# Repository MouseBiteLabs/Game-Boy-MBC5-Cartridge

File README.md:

# Game Boy MBC5 Cartridge

This is my design of a flashable MBC5-based cartridge for the Game Boy. The MBC5 mapper greatly augments the memory access of the Game Boy for larger games. Most of the games that came out in the last years of the Game Boy and Game Boy Color used the MBC5 mapper.

This circuit board should cover most MBC5 games. The features are as follows:

- Able to make games up to 4 MB in size, that use up to 1 Mbit of RAM
- Compatibility with all four of the popular Game Boy battery management ICs - MM1026, MM1134, BA6129, and BA6735
- The option to add battery backup to the cartridge *without* the need of the original battery management ICs - perfect for MBC5 donors that didn't have batteries in them
- Fully compatible with the <a href="https://www.gbxcart.com/">GBxCart RW</a> so you can transfer games and save files to and from the board

All gerbers and source files can be found in this repo, as this project is fully open source. Technical documentation of the board can be found in the Technical folder.

## Important Things Before You Start

1) To use this board, you need to have an original Game Boy game that uses an MBC5 mapper chip. <a href="https://catskull.net/gb-rom-database/">You can find a list of games and their mappers here</a>. Use the search function. Please note the RAM is in bytes, not bits. Since SRAM in this repo is defined in bits, you need to convert by multiplying the number of bytes by 8.
2) You will need to remove the MBC5 from your donor cartridge for use on this board. This will require a hot air rework station or a hot plate. There's a list below of other parts you can re-use from the donor cartridge.
3) When soldering parts on, it's a good idea to put kapton tape or otherwise cover the bottom cartridge edge. You do not want to get solder on the cartridge contacts.
4) I am not responsible for any damage you do to your self or your property. Attempt this project at your own risk.
5) I do not guarantee design compatibility. You may encounter issues with certain games. There is also a chance I have made an error in the design or the BOM - if this is the case, I will do everything I can to address the problem as quickly as possible.
6) If you are using this board to make games other than for personal use, you must have permission from the originator to use and distribute any ROM images or other related material. You are responsible for making sure you adhere to any license requirements.

DO NOT use my circuit boards for profiting from stolen work - this especially includes homebrew content, ROM hacks, and using fan-made labels without permission from the originator. **Support original creators!**

## Board Characteristics and Order Information

The zipped folder contains all the gerber files for this board. The following options **must** be chosen when ordering boards for yourself.

- Thickness: 0.8mm
- Surface Finish: ENIG
- Gold Fingers: Yes, 30° chamfer

**I sell this blank circuit board on Etsy, so you don't have to buy a bunch of multiples if you don't want to.** (Click the banner!)

You can use the zipped folder at any board fabricator you like. You may also buy the board from PCBWay using this link (disclosure: I receive 10% of the sale value to go towards future PCB orders of my own):

<a href="https://oshpark.com/shared_projects/rcPGJGK0">The board is also listed on OSH Park as well.</a> **Be sure to get them in 0.8mm thickness if you order from here.**

## Required Equipment

The EEPROMs on the board needs to be programmed somehow. I recommend using the GBxCart, as mentioned. These boards are fully compatible with it, and it makes reflashing games extremely easy using <a href="https://github.com/lesserkuma/FlashGBX">lesserkuma's FlashGBX software</a>.

Alternatively, you can buy an EEPROM programmer with a TSOP adapter. The downside to this method is that you have to desolder the chip every time you want to program it. The <a href="https://flashcatusb.com/">FlashcatUSB</a> is one popular option in retro spaces.

## Battery Safety

When assembling a board, I recommend populating all the parts *except* the battery, and getting it to run initially without it. This is to make it easier to fix any solder connections that might need fixing, without having to worry about getting the battery hot. And if you need to rework anything near the battery after you've put it on the board, be safe and remove it before putting a hot soldering iron next to it.

And this should go without saying, but if you're assembling these boards with a hot plate or hot air, *do not* solder the battery on this way. You should use an iron, and keep heat off of the battery as much as possible. 

(Also check polarity!)

## Board Configurations

The board comes with three sets of jumper pads for solder bridges. SJ1 and SJ2 require you to solder bridge the middle pad either to the left or right pads. SJ3 is configured by either leaving the pads unsoldered or bridging them with solder. Here are the situations where you need to add solder bridges.

### SRAM Size Selection (SJ1 and SJ2, or SW1)

These jumpers are located underneath the MBC5 chip, and labeled "64K" and "256K/1M". Solder them to configure the amount of RAM your cart uses. You must configure these pads for every game you make, unless you do not need RAM. <a href="https://catskull.net/gb-rom-database/">You can find a list of games here with their respective RAM sizes.</a>

- If the game you're making uses 256 Kbit or 1 Mbit of RAM, then solder the middle pads of the two jumper sets to the right pads.
- If the game you're making uses 64 Kbit of RAM, then solder the middle pads of the two jumper sets to the left pads.
- SJ1 and SJ2 must be soldered in the same direction.
- The footprint of these selection pads should allow for a DPDT switch, part number CAS-220A1, to be placed on these pads instead of having to bridge the pads with solder.

Note that you can make games that only require 64 Kbit of RAM and still use a 256 Kbit or 1 Mbit SRAM chip. You still need to configure the jumpers to the 64Kb setting, though.

**I recommend using 64 Kbit or 256 Kbit RAM chips, unless you absolutely need 1 Mbit for the game you are making.**

### Using an MM1134 or BA6735 for U4 (SJ3)

Bridge the jumper SJ3 if you have either an MM1134 or BA6735 for U4, specifically. Any other battery management IC must leave SJ3 unsoldered.

## Test Points and Final Checkout

On the back of the board are five test points. Here's where they are connected:

- TP1: SRAM supply voltage
- TP2: Battery voltage (after R1)
- TP3: Battery voltage (positive terminal of battery)
- TP4: Ground
- TP5: VCC input voltage

After you assemble your game, you should measure the current out of the battery. But first, you should program it with the GBxCart, or if you programmed the EEPROM separately, put it into a Game Boy and cycle power once. Then, flip the PCB upside down on a non-conductive surface (not your leg), and set your multimeter in DC millivolts (or volts). Put the positive probe on TP3 and the negative probe on TP2. If you used a 10kΩ for R1, as indicated in the BOM, you should read a voltage in the single of millivolts. If you have something much higher, especially voltages above 20mV, then you likely have an issue or short circuit on the board somewhere.

**Note: You need to power up the game at least once before battery currents will make sense - the battery management ICs can start up in an unknown state before applying main power to the board.**

To estimate battery life, see <a href="https://github.com/MouseBiteLabs/Game-Boy-MBC5-Cartridge/tree/main/Technical#estimating-battery-life">this section in the Technical Design Document</a>, or for more in-depth analysis, <a href="https://hackaday.io/project/11864-tritiled/log/72554-determining-maximum-runtime-176-to-202-years-cr2032">this Hackaday post</a>.

### Why not FRAM?

This board is only suitable for using SRAM. One downside to SRAM, if you haven't figured it out yet, is that you need a battery to keep the SRAM powered on even when the game is turned off. So eventually the battery will die, and your save data is lost. Some people have used FRAM, or Ferroelectric RAM, to keep save data around even after the battery dies (specifically, the popular part that's used for FRAM carts is the FM18W08). But, using this FRAM chip has a handful of downsides, and the benefit of keeping save data after the battery dies *in my opinion* does not outweigh the cons, which are as follows:

1) Quality, new stock, 5V tolerant FRAM is expensive ($12+ per part).
2) Cheaper FRAM chips from eBay or Aliexpress are notoriously flaky (anecdotally, ~50% success rate).
3) FRAM memory access requires different chip select timing than SRAM, and the Game Boy expects SRAM, so it is not natively compatible with FRAM carts. The Gameboy Color specifically cannot (easily) be made to properly access FM18W08 chip. You *can* use an OR gate and add the CLK on the cart edge to try to achieve the necessary timing, but it only works (properly) for DMG/MGB/SGB, not the GBC. It usually *works* in practice for GBC, but it's technically a datasheet violation and can potentially cause issues in edge cases. <a href="https://github.com/Gekkio">(Thanks to gekkio for pointing this out!)</a>

Brand new SRAM chips are ~$3, and having the SRAM footprint also allows you to use SRAM from an original cart if desired. You will *easily* get more than a decade of life running on a battery. You're already assembling this cartridge; you can dump the save and replace the battery before then!

Note that this isn't to throw shade at any FRAM-based carts, but for me personally, it's more trouble than it's worth. If you just *need* FRAM, you can find other cart designs out there that have it, <a href="https://github.com/HDR/MBC5-Flashcart">like this one!</a>

## Board Fitment

The shape of this board was originally meant to mimic original Game Boy circuit boards as closely as possible (v1.3 and earlier). Unfortunately, when placed in some aftermarket Game Boy cartridge shells (like those from Cloud Game Store), the circuit board has a lot of freedom to rotate around the main screw hole in the bottom-middle of the cartridge. This can cause misalignment when you put it in a Game Boy, which can cause a game to either not load properly (garbled Game Boy logo) or shut off the Game Boy because of a short circuit. This isn't *dangerous* or anything, just annoying.

In order to make the boards fit nicer in any kind of shell, for v1.4 I added extended tabs of circuit board material to the edges of the cartridges to keep it from rotating too much in shells, which was suggested to me by <a href="https://github.com/orangeglo">orangeglo</a>! (Thanks!)

If you're having trouble fitting the circuit board into a shell, because the tabs interfere with the cart edges, you can safely sand or trim them down as there is no copper within the tabs themselves. The only shell that appears to require any kind of trimming are Kitsch-Bent shells.

## Bill of Materials (BOM)

Your parts list will vary depending on the game you are trying to make, and what chips you have for the battery management (if any). **You cannot use both U4 and U5 - you must choose one or the other.** U4 comes from a donor cartridge, and U5 is a readily available aftermarket option.

Please carefully review the parts you need for the board you are trying to make. Do not add any parts to your build that don't appear in the column for the game you are making. This means you *cannot* populate every component on the board at the same time.

| Reference Designators | Value/Part Number              | Package          | Description        | No save carts | Save carts with MM1134 or BA6735 | Save carts with MM1026 or BA6129 | Save carts without donor U4 chip | Source                                           |
| --------------------- | ------------------------------ | ---------------- | ------------------ | ------------- | -------------------------------- | -------------------------------- | -------------------------------- | ------------------------------------------------ |
| B1                    | CR2032, CR2025, CR2016         | CR2032           | Backup Battery     |               | X                                | X                                | X                                | [https://mou.sr/3SeAzfT](https://mou.sr/3SeAzfT) |
| C1                    | 0.1uF                          | 0603             | Capacitor (MLCC)   | X             | X                                | X                                | X                                | [https://mou.sr/3ENc15O](https://mou.sr/3ENc15O) |
| C4                    | 0.1uF                          | 0603             | Capacitor (MLCC)   | X             | X                                | x                                |                                  | [https://mou.sr/3ENc15O](https://mou.sr/3ENc15O) |
| C5                    | 0.1uF                          | 0603             | Capacitor (MLCC)   |               | X                                | X                                | X                                | [https://mou.sr/3ENc15O](https://mou.sr/3ENc15O) |
| C6                    | 10uF                           | 0603             | Capacitor (MLCC)   |               | X                                | X                                | X                                | [https://mou.sr/3mZtSkF](https://mou.sr/3mZtSkF) |
| C7                    | 0.1uF                          | 0603             | Capacitor (MLCC)   | X             | X                                | X                                | X                                | [https://mou.sr/3ENc15O](https://mou.sr/3ENc15O) |
| C8                    | 0.1uF                          | 0603             | Capacitor (MLCC)   |               |                                  |                                  | X                                | [https://mou.sr/3ENc15O](https://mou.sr/3ENc15O) |
| Q1                    | 2N7002                         | SOT-23           | N-Channel FET      |               |                                  |                                  | X                                | [https://mou.sr/3rgfh6J](https://mou.sr/3rgfh6J) |
| Q2                    | 2N7002                         | SOT-23           | N-Channel FET      |               |                                  | X                                |                                  | [https://mou.sr/3rgfh6J](https://mou.sr/3rgfh6J) |
| R1                    | 10k                            | 0603             | Resistor           |               | X                                | X                                | X                                | [https://mou.sr/3riR7IH](https://mou.sr/3riR7IH) |
| R7                    | 10k                            | 0603             | Resistor           |               |                                  | X                                |                                  | [https://mou.sr/3riR7IH](https://mou.sr/3riR7IH) |
| R8                    | 10k                            | 0603             | Resistor           | X             | X                                | X                                | X                                | [https://mou.sr/3riR7IH](https://mou.sr/3riR7IH) |
| R9                    | 130k                           | 0603             | Resistor           |               |                                  |                                  | X                                | [https://mou.sr/3MjXliy](https://mou.sr/3MjXliy) |
| R10                   | 49.9k                          | 0603             | Resistor           |               |                                  |                                  | X                                | [https://mou.sr/3Q3NRZO](https://mou.sr/3Q3NRZO) |
| U1                    | 29F016, 29F032, 29F033         | TSOP-48, TSOP-40 | Flash EEPROM       | X             | X                                | X                                | X                                | AliExpress or eBay                               |
| U2                    | MBC5                           | QFP-32           | MBC5 Mapper        | X             | X                                | X                                | X                                | Donor MBC5 Game Boy cartridge                    |
| U3                    | AS6C6264, AS6C62256, AS6C1008  | SOP-28, SOP-32   | SRAM               |               | X                                | X                                | X                                | [https://mou.sr/3ZxG6jd](https://mou.sr/3ZxG6jd) |
| U4                    | MM1026, MM1134, BA6129, BA6735 | SOIC-8           | Battery Management |               | X                                | X                                |                                  | Donor Game Boy cartridge                         |
| U5                    | TPS3613                        | MSOP-10          | Battery Management |               |                                  |                                  | X                                | https://mou.sr/45Ir2kh                           |

*Note that C9 - C11 footprints are only included on the board for strange edge cases that may require them sometime in the future; do not populate! See the technical design document for more information.*

### Usable Donor Cartridge Parts

You can use a few parts from the donor cart on the new board to save some money. Note that you will generally get better reliability with new parts as opposed to old ones. For example: I have seen failed RAM chips from donors in the past.

1) **U2: MBC5** - This one is required
2) **U3: SRAM** - You can use this part *only if* the game you're making uses the same or less amount of RAM that the donor cartridge does
3) **U4: Battery Management IC** - Using this is probably preferred over the TPS3613 because it'll save you money and parts to put on

You could probably transfer over most of the 0.1uF capacitors but they're pretty cheap anyway, so I generally just recommend buying new resistors and capacitors.

### Capacitors C9 to C11

If you want to experiment with the capacitors C9 to C11, see this info below. **Be aware that adding these components in some of my tests actually ***stopped*** games from working, so again, assume that if you have a problem it lies elsewhere first, because it almost certainly does.**
- C9 is a capacitor connected nearby the SRAM's /WE pin to GND. These were populated on some cartridges, and I believe have a value of approximately 1 nF (0.001 uF) based on measurements from an MBC1 board that used it.
- C10 is a capacitor connected from the cart edge /RESET pin to GND. A spot for this capacitor was included on some MBC5 carts, but I cannot locate an instance of it actually being used when looking through the gbhwdb. I don't actually know what value this capacitor would need to be, so I am guessing 1 nF.
- C11 is a capacitor that I have added that was not used on any original Game Boy board. It connects to the SRAM's /CE pin, bypassing to GND. I have added this in the event incompatibilities arise with newer SRAM chips that have much faster speeds than older SRAM chips. This was a problem I encountered on some of my NES cartridges, so this is here just in case, but I have not found an instance where it's required.

## Things to Remember

- The footprint for the EEPROM is specifically for 29F016 - it has 48 pins. However, 29F032 and 29F033 are only 40 pin devices. They still work fine on the board though - place them in the center of the footprint, and leave the outer two pins on each corner empty
- The 29F016, 29F032, and 29F033 have been known to occasionally be defective upon arrival. They're either used, or new old stock, and usually only available from AliExpress.
- The footprint for the battery can fit a CR2032, CR2025, or CR2016 with solder tabs. The only difference is the mAh capacity (larger number = longer life). If you get Panasonic tabbed batteries, you may have to trim the battery tabs to make them fit on the footprint.
  - For untabbed coin cells, you can find battery retainer adapters online, <a href="https://retrogamerepairshop.com/products/hdr-game-boy-game-battery-retainer?variant=40511013290156">like this one,</a> but only for board revision v1.4. It will not fit on earlier revisions.
- For battery management, use either U4 *or* U5 and supporting components. **Do not** use U4 and U5 simultaneously on one board. They will interfere with each other.
- Generally, ROM sizes are conveyed in terms of kilo**bytes** and mega**bytes** (KB, MB). RAM size is usually conveyed in terms of kilo**bits** or mega**bits** (Kbit, Mbit). You can convert Kbit and Mbit to KB and MB by dividing Kbit or Mbit by 8. For example, 256 Kbit = 32 KB.
- You only need to provide ROM and RAM chips that have at least *or greater* the size of the game you are trying to make. That means you can use a 256 Kbit SRAM chip for a game that only requires 64 Kbit of RAM!

## Labels

If you want a Bucket Mouse branded label for your cartridge, look no further than <a href="https://krizdingus.com/mousebitelabs/">krizdingus's designs</a>. Special thanks to Kris for designing these, they look awesome! (If you are going to order/print these, use the high-res images hosted on his website, and *keep the labels for personal or non-commercial use only.*)

## Revision History

### v1.4
- Reduced cart edge by 0.1 mm for better fitment
- Adjusted battery placement to support more battery holders
- Added tabs on the board edges to allow the circuit board to fit better in aftermarket cartridge shells

### v1.3
- Extended cart edge down by 0.25 mm for better fitment
- Added OSHW logo and "SUPPORT ORIGINAL CREATORS!"

### v1.2
- Replaced non-donor battery management circuitry with a TPS3613-based circuit for smaller BOM and easier routing
  
### v1.1
- Moved all parts on the top down to allow for compatibility with DMG-style shells
- Rotated battery for more space
- Widen SRAM footprint for easier soldering
- Renamed some reference designators for consistency between designs
- Changed silkscreen for clarity
- Removed multicart option

### v1.0
- Release revision

## Resources and Acknowledgements

- <a href="http://www.devrs.com/gb/files/hardware.html">Jeff Frohwein's GameBoy Tech Page</a>
- <a href="https://gbhwdb.gekkio.fi/">Game Boy Hardware Database</a>
- <a href="https://catskull.net/gb-rom-database/">Nintendo Gameboy Game List</a>
- <a href="https://www.gbxcart.com/">insideGadgets discord server for GBxCart RW compatibility requirements</a>
- <a href="https://github.com/lesserkuma/FlashGBX">Lesserkuma's FlashGBX software</a>
- <a href="https://www.alldatasheet.com/datasheet-pdf/pdf/99104/MITSUBISHI/MM1026.html">System Reset IC Datasheet</a>
- <a href="https://www.ti.com/lit/ds/symlink/tps3613-01.pdf?HQS=dis-mous-null-mousermode-dsf-pf-null-wwe&ts=1698238885366&ref_url=https%253A%252F%252Feu.mouser.com%252F">TPS3613 Datasheet</a>
- Board outline modified from <a href="https://tinkerer.us/projects/homebrew-gameboy-cartridge.html">Dillon Nichols's Homebrew Gameboy Cartridge project</a>
- Thanks to <a href="https://github.com/orangeglo">orangeglo</a> for his suggestion of adding spacers around the board edge for better fitment in aftermarket cartridges
- Some components from <a href="https://github.com/adafruit/Adafruit-Eagle-Library">Adafruit's Eagle parts library</a>
- Some components from <a href="https://www.snapeda.com/">SnapMagic</a>
- Thank you to <a href="https://github.com/Gekkio">gekkio</a> for their deep Game Boy knowledge resources, and for collaboration in demystifying some of the design choices on Game Boy cartridges
- Thanks to the awesome members of the <a href="https://moddedgameboy.club/">Modded Gameboy Club</a> for their feedback and support during the entire project development

## License

<br />This work is licensed under a <a rel="license" href="http://creativecommons.org/licenses/by-sa/4.0/">Creative Commons Attribution-ShareAlike 4.0 International License</a>. You are able to copy and redistribute the material in any medium or format, as well as remix, transform, or build upon the material for any purpose (even commercial) - but you **must** give appropriate credit, provide a link to the license, and indicate if any changes were made.

©MouseBiteLabs 2023

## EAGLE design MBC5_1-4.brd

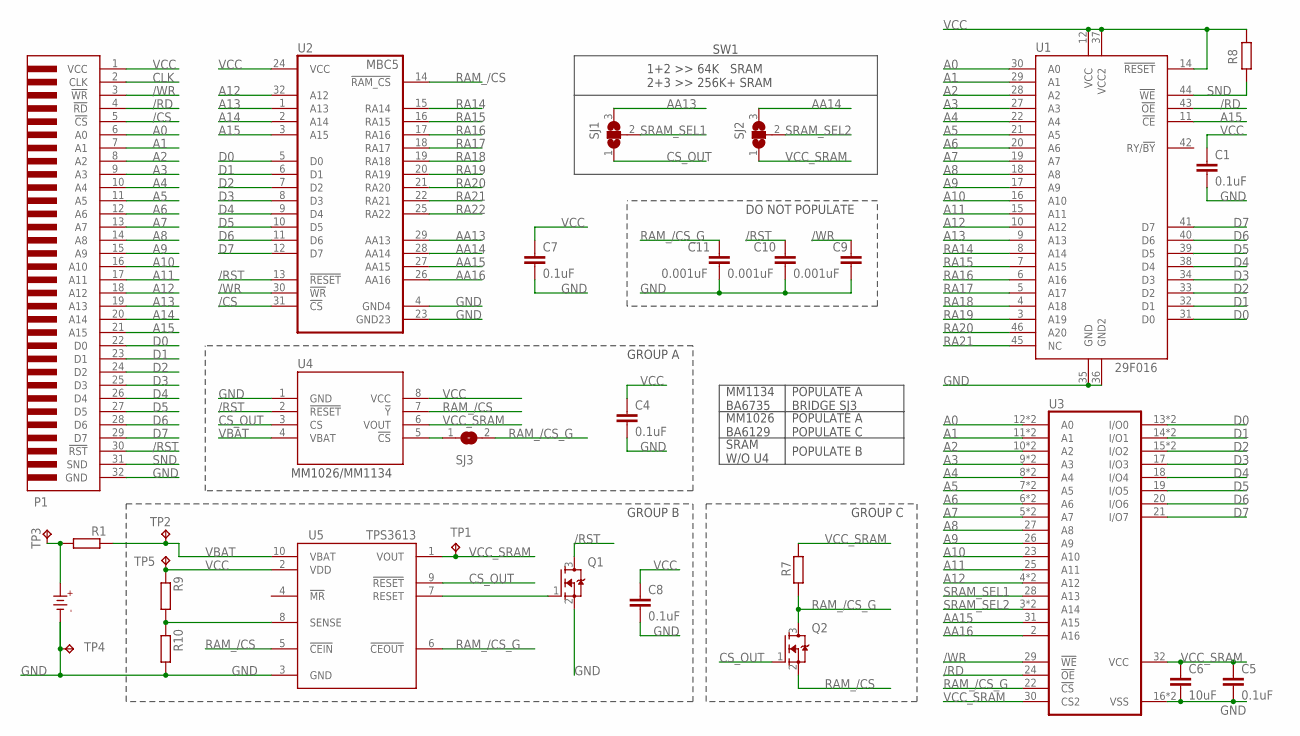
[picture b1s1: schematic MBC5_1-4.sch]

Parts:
B1: CR2025
C1, C4, C5, C7, C8: 0.1uF; C0603
C6: 10uF; C0603
C9, C10, C11: 0.001uF; C0603
P1: GBC_CARTTAB; GBC_CART_TABBED
Q1, Q2: 2N7002; SOT23
R1, R7, R8, R9, R10: RR0603; R0603
SJ1, SJ2: SJ2W; SJ_2
SJ3: SJ
TP1, TP2, TP3, TP4, TP5: TPB1,27; B1,27
U1: 29F016; TSOP-48
U2: MBC5; QFP-32
U3: 1008L; SO32L_L
U4: MM1134; SOIC-8
U5: TPS3613; MSOP-10

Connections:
/CS: P1.5 (!CS), U2.31 (!CS)
/RD: P1.4 (!RD), U1.43 (!OE), U3.24 (!OE)
/RST: C10.1, P1.30 (!RST), Q1.3 (D), U2.13 (!RESET), U4.2 (!RESET)
/WR: C9.1, P1.3 (!WR), U2.30 (!WR), U3.29 (!WE)
A0: P1.6 (A0), U1.30 (A0), U3.12 (A0), U3.L12 (A0)
A1: P1.7 (A1), U1.29 (A1), U3.11 (A1), U3.L11 (A1)
A2: P1.8 (A2), U1.28 (A2), U3.10 (A2), U3.L10 (A2)
A3: P1.9 (A3), U1.27 (A3), U3.9 (A3), U3.L9 (A3)
A4: P1.10 (A4), U1.22 (A4), U3.8 (A4), U3.L8 (A4)
A5: P1.11 (A5), U1.21 (A5), U3.7 (A5), U3.L7 (A5)
A6: P1.12 (A6), U1.20 (A6), U3.6 (A6), U3.L6 (A6)
A7: P1.13 (A7), U1.19 (A7), U3.5 (A7), U3.L5 (A7)
A8: P1.14 (A8), U1.18 (A8), U3.27 (A8)
A9: P1.15 (A9), U1.17 (A9), U3.26 (A9)
A10: P1.16 (A10), U1.16 (A10), U3.23 (A10)
A11: P1.17 (A11), U1.15 (A11), U3.25 (A11)
A12: P1.18 (A12), U1.10 (A12), U2.32 (A12), U3.4 (A12), U3.L4 (A12)
A13: P1.19 (A13), U1.9 (A13), U2.1 (A13)
A14: P1.20 (A14), U2.2 (A14)
A15: P1.21 (A15), U1.11 (!CE), U2.3 (A15)
AA13: SJ1.3, U2.29 (AA13)
AA14: SJ2.3, U2.28 (AA14)
AA15: U2.27 (AA15), U3.31 (A15)
AA16: U2.26 (AA16), U3.2 (A16)
CLK: P1.2 (CLK)
CS_OUT: Q2.1 (G), SJ1.1, U4.3 (CS), U5.9 (!RESET)
D0: P1.22 (D0), U1.31 (D0), U2.5 (D0), U3.13 (I/O0), U3.L13 (I/O0)
D1: P1.23 (D1), U1.32 (D1), U2.6 (D1), U3.14 (I/O1), U3.L14 (I/O1)
D2: P1.24 (D2), U1.33 (D2), U2.7 (D2), U3.15 (I/O2), U3.L15 (I/O2)
D3: P1.25 (D3), U1.34 (D3), U2.8 (D3), U3.17 (I/O3)
D4: P1.26 (D4), U1.38 (D4), U2.9 (D4), U3.18 (I/O4)
D5: P1.27 (D5), U1.39 (D5), U2.10 (D5), U3.19 (I/O5)
D6: P1.28 (D6), U1.40 (D6), U2.11 (D6), U3.20 (I/O6)
D7: P1.29 (D7), U1.41 (D7), U2.12 (D7), U3.21 (I/O7)
GND: B1.-, C1.2, C4.2, C5.2, C6.2, C7.2, C8.2, C9.2, C10.2, C11.2, P1.32 (GND), Q1.2 (S), R10.2, TP4.TP, U1.35 (GND), U1.36 (GND2), U2.4 (GND4), U2.23 (GND23), U3.16 (VSS), U3.L16 (VSS), U4.1 (GND), U5.3 (GND)
unnamed: B1.+, R1.2, TP3.TP
unnamed: SJ3.1, U4.5 (!CS)
unnamed: Q1.1 (G), U5.7 (RESET)
unnamed: R9.2, R10.1, U5.8 (SENSE)
RA14: U1.8 (A14), U2.15 (RA14)
RA15: U1.7 (A15), U2.16 (RA15)
RA16: U1.6 (A16), U2.17 (RA16)
RA17: U1.5 (A17), U2.18 (RA17)
RA18: U1.4 (A18), U2.19 (RA18)
RA19: U1.3 (A19), U2.20 (RA19)
RA20: U1.46 (A20), U2.21 (RA20)
RA21: U1.45 (NC), U2.22 (RA21)
RA22: U2.25 (RA22)
RAM_/CS: Q2.2 (S), U2.14 (!RAM_CS), U4.7 (!Y), U5.5 (!CEIN)
RAM_/CS_G: C11.1, Q2.3 (D), R7.1, SJ3.2, U3.22 (!CS), U5.6 (!CEOUT)
SND: P1.31 (SND), R8.2, U1.44 (!WE)
SRAM_SEL1: SJ1.2, U3.28 (A13)
SRAM_SEL2: SJ2.2, U3.3 (A14), U3.L3 (A14)
VBAT: R1.1, TP2.TP, U4.4 (VBAT), U5.10 (VBAT)
VCC: C1.1, C4.1, C7.1, C8.1, P1.1 (VCC), R8.1, R9.1, TP5.TP, U1.12 (VCC), U1.14 (!RESET), U1.37 (VCC2), U2.24 (VCC), U4.8 (VCC), U5.2 (VDD)
VCC_SRAM: C5.1, C6.1, R7.2, SJ2.1, TP1.TP, U3.30 (CS2), U3.32 (VCC), U4.6 (VOUT), U5.1 (VOUT)

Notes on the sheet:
1+2 >> 64K SRAM 2+3 >> 256K+ SRAM
GROUP A
MM1026/MM1134
GROUP B
GROUP C
DO NOT POPULATE
SW1
MM1134 BA6735
POPULATE A BRIDGE SJ3
MM1026 BA6129
POPULATE A POPULATE C
SRAM W/O U4
POPULATE B

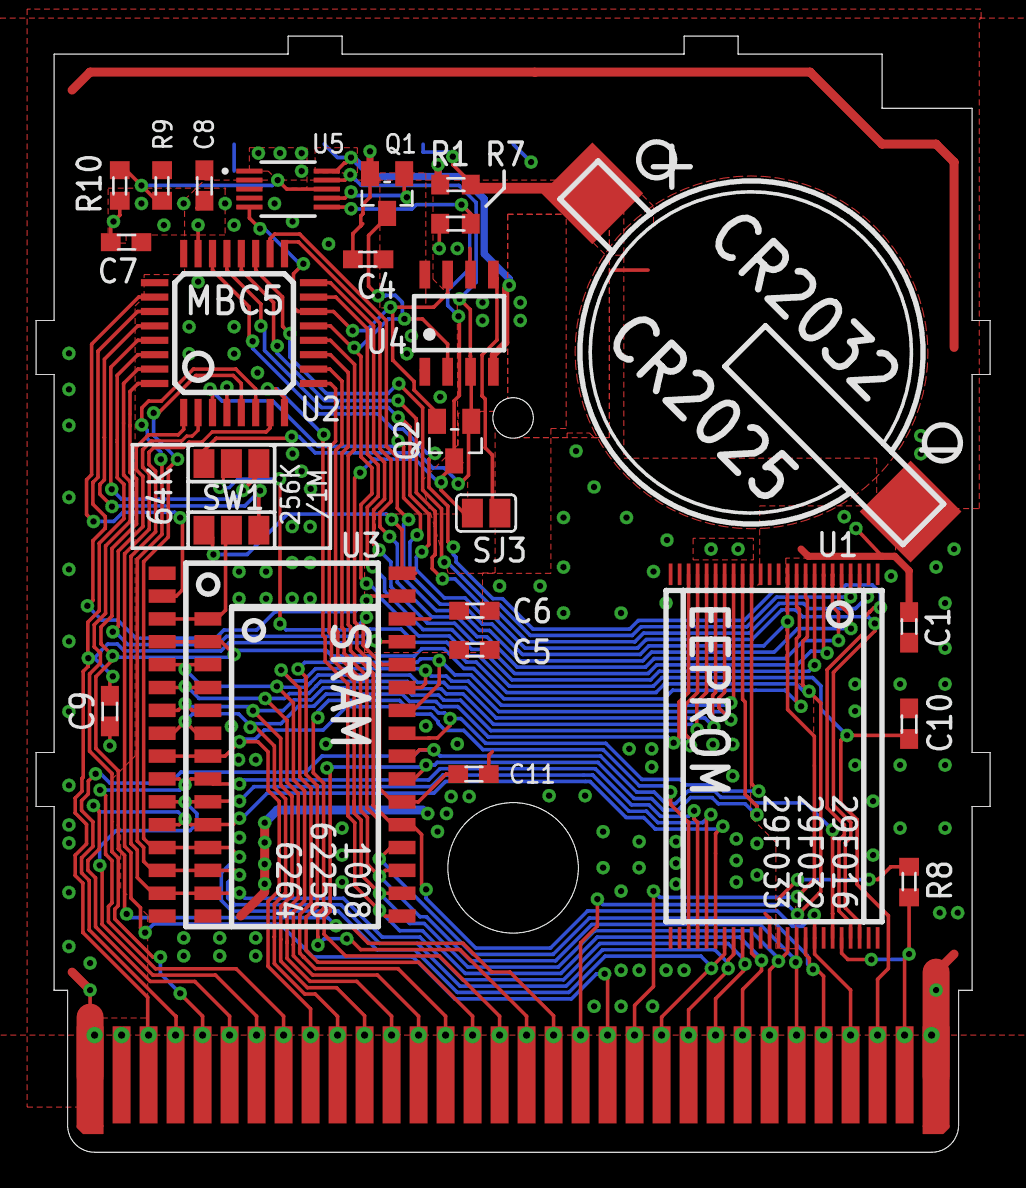
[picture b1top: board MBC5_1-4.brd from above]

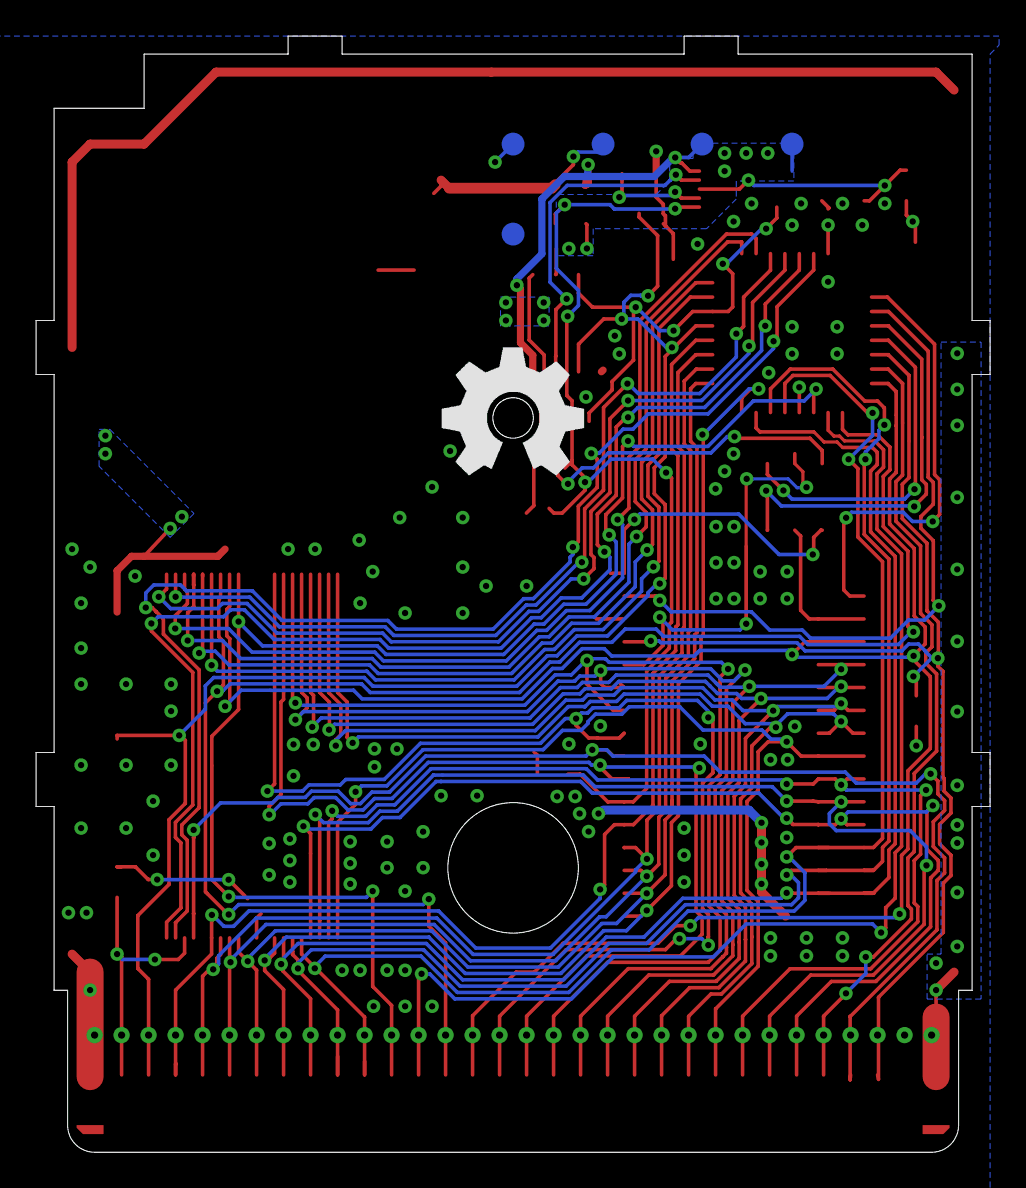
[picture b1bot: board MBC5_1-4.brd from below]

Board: 2 copper layers, 53.0 x 62.0 mm, 31 parts (5 on the bottom side), 54 nets.

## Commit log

2024-10-23 Rename LICENSE.MD to LICENSE.md
2025-01-07 Update README.md
    Fixed a copy-paste error

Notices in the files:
README.md:
This work is licensed under a Creative Commons Attribution-ShareAlike 4.0 International License. You are able to copy and redistribute the material in any medium or format, as well as remix, transform, or build upon the material for any purpose (even commercial) - but you **must** give appropriate credit, provide a link t
©MouseBiteLabs 2023
